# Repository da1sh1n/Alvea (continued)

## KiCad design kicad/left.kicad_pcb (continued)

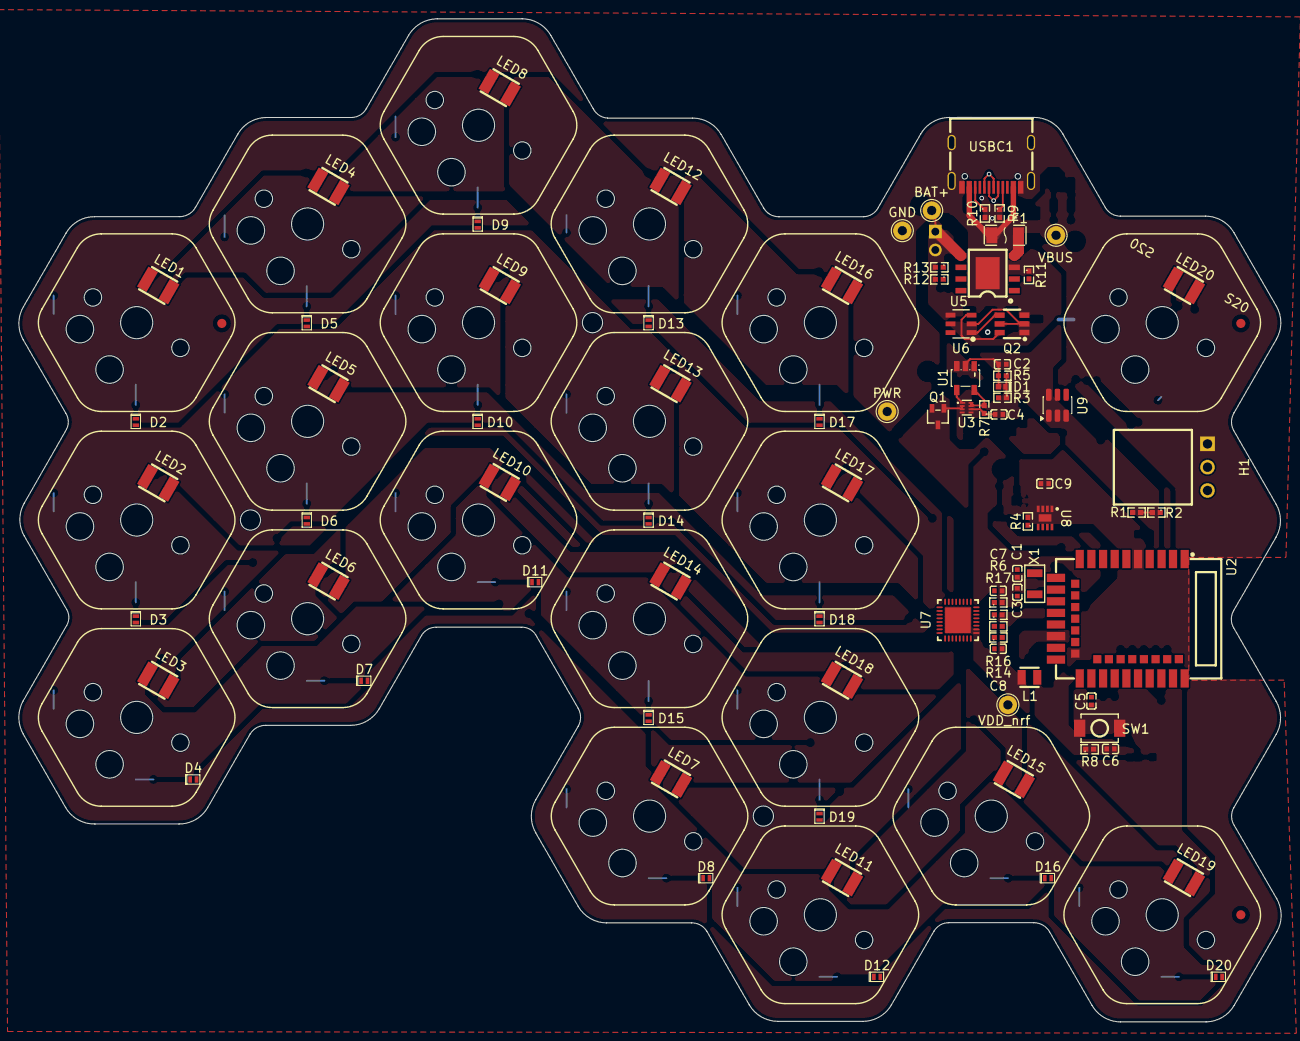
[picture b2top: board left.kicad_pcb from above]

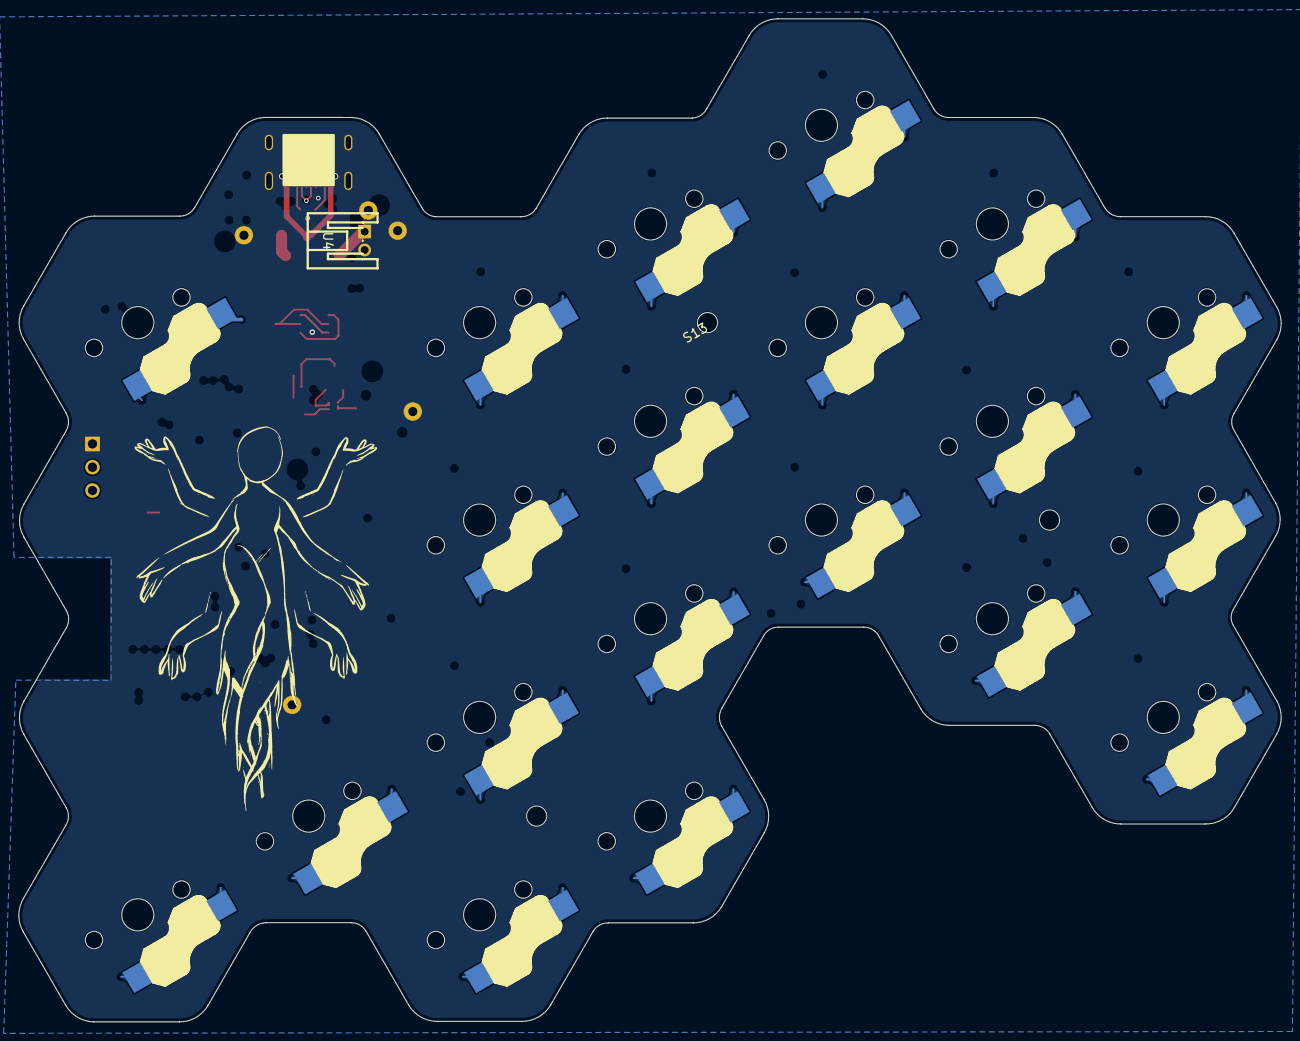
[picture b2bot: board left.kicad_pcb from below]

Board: 4 copper layers, 137.5 x 109.3 mm, 111 parts (2 on the bottom side), 82 nets.

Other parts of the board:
BAT+: TestPoint_THTPad_D2.0mm_Drill1.0mm
Fi1, Fi2, Fi3: Fiducial_1mm_Mask2mm
G**: LOGO; handy
GND: TestPoint_THTPad_D2.0mm_Drill1.0mm
PWR: TestPoint_THTPad_D2.0mm_Drill1.0mm
VBUS: TestPoint_THTPad_D2.0mm_Drill1.0mm
VDD_nrf: TestPoint_THTPad_D2.0mm_Drill1.0mm

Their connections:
/BAT+: BAT+.1; also elsewhere on the board
/PWR: PWR.1; also elsewhere on the board
/VBUS: VBUS.1; also elsewhere on the board
/VDD_nRF: VDD_nrf.1; also elsewhere on the board
GND: GND.1; also elsewhere on the board
